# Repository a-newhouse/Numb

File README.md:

# Disclaimer
This is my first attempt, with [Duality](https://github.com/a-newhouse/Duality), to make a fully functional keyboard from A to Z. 
# Schematic
To start with, I knew I wanted to use an RP2040 and per key LEDs. So I searched how to make an RP2040 board amd i found a book made by Raberry PI called the [Hardware design with RP2040: Using RP2040 microcontrollers to build boards and products](./Schematic_&_PCB/Hardware_Design_RP2040.pdf). This book contains alot of information on how to make a RP2040 development board.
# PCB
# 3D modeling
# BOM
# Assembly
# QMK Firmware

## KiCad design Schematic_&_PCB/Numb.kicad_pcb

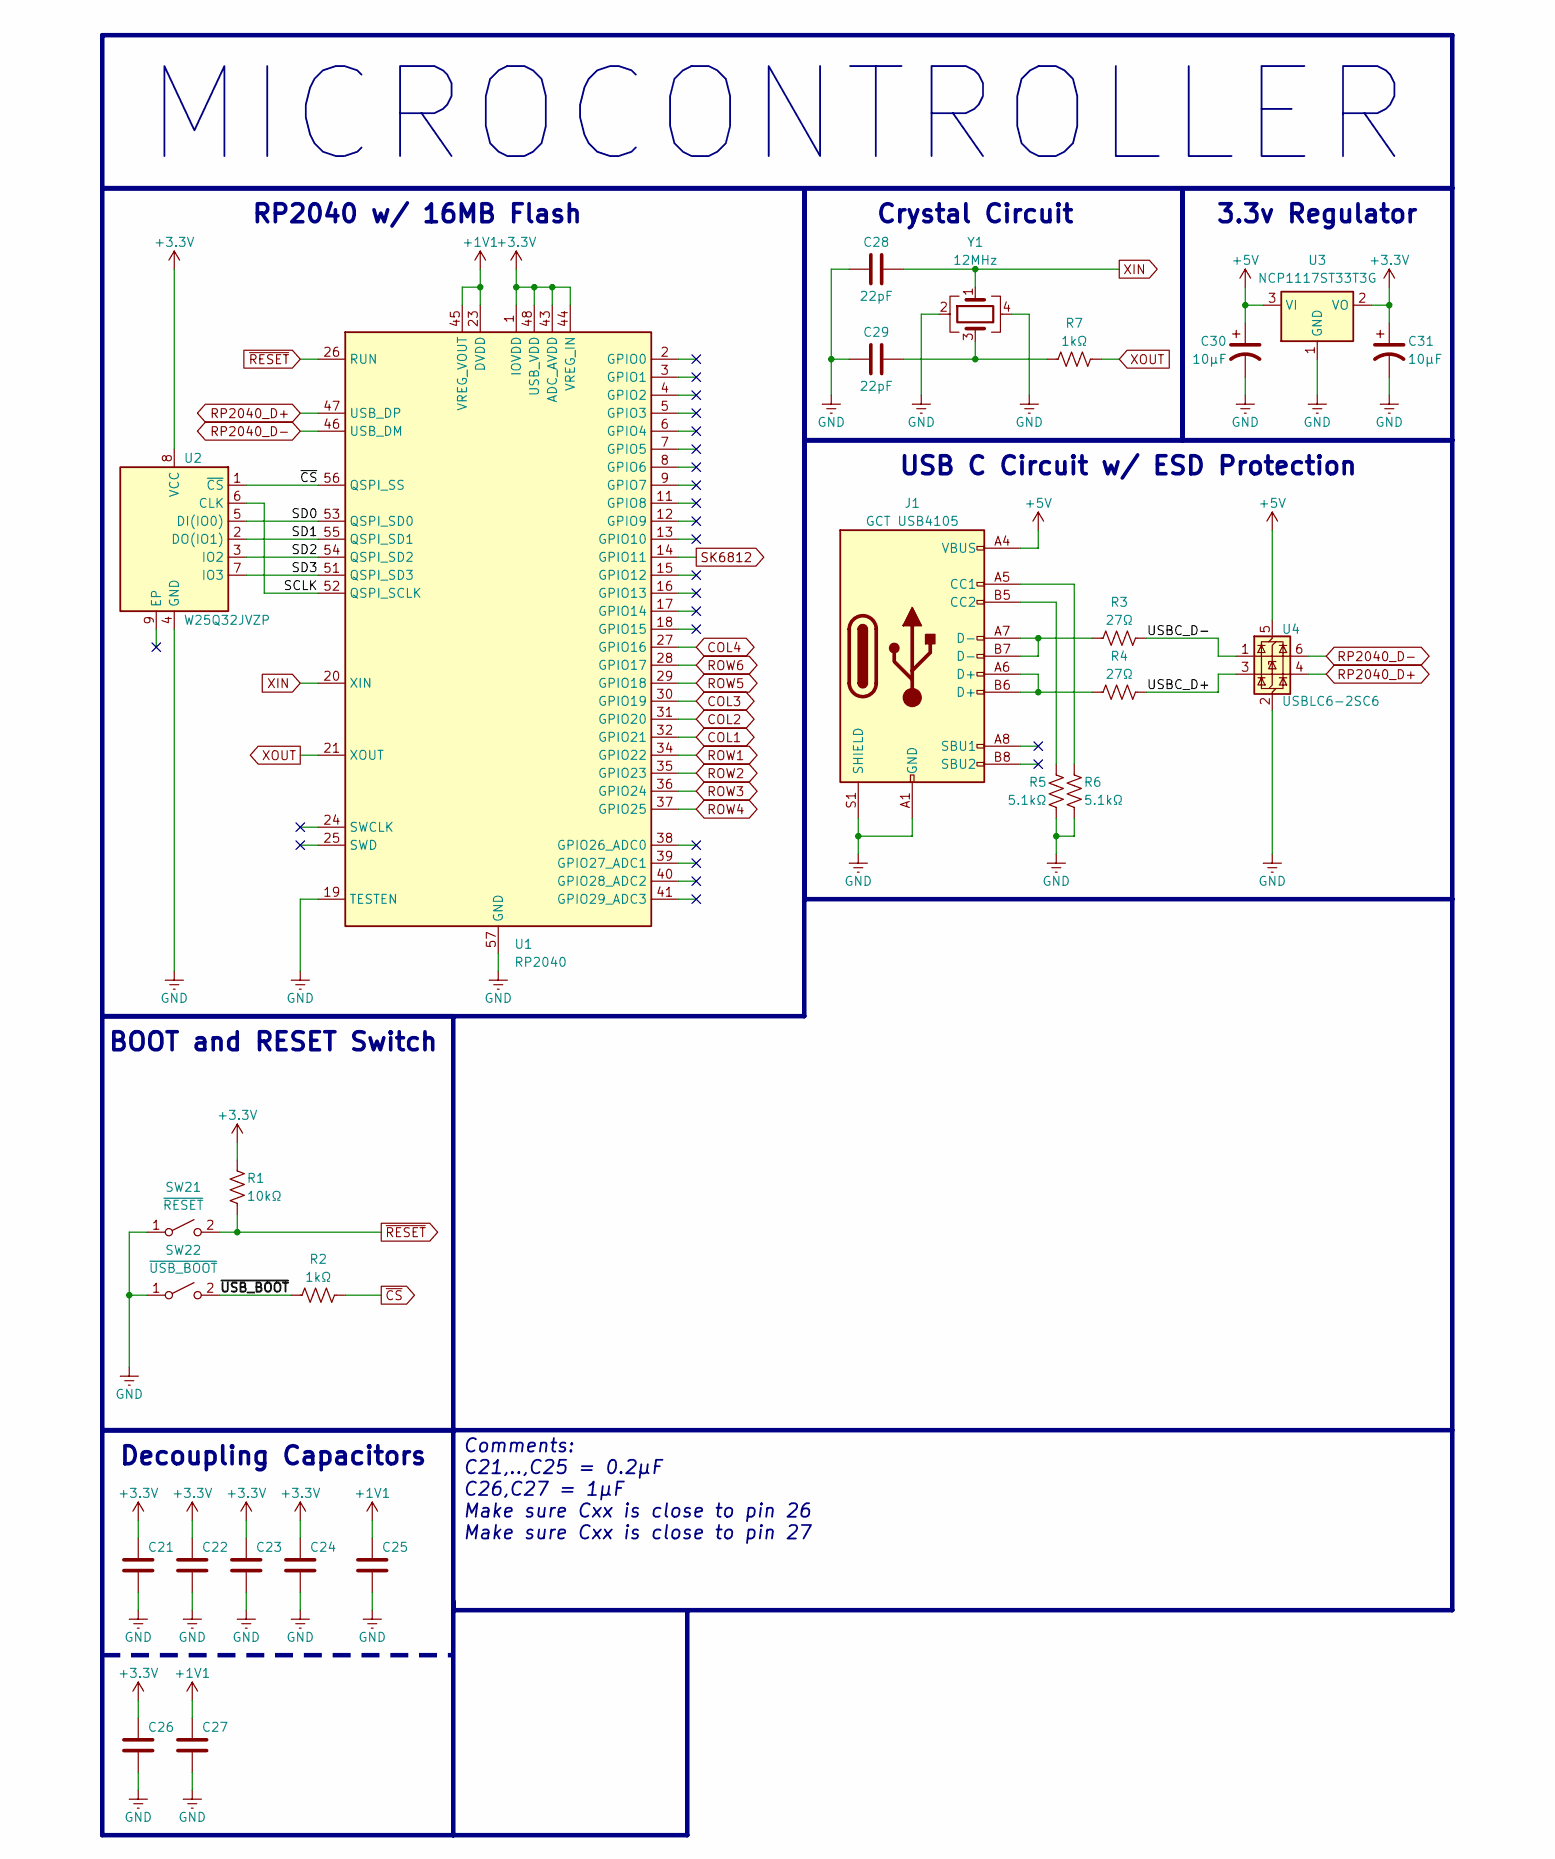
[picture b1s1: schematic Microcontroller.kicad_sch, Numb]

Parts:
C21, C22, C23, C24, C25: 0.2μF; C_0603_1608Metric
C26, C27: 1μF; C_0603_1608Metric
C28, C29: 22pF; C_0402_1005Metric
C30, C31: 10μF; CP_EIA-3216-10_Kemet-I
J1: GCT USB4105; USB_C_Receptacle_GCT_USB4105-xx-A_16P_TopMnt_Horizontal
R1: 10kΩ; R_0402_1005Metric
R2, R7: 1kΩ; R_0402_1005Metric
R3, R4: 27Ω; R_0603_1608Metric
R5, R6: 5.1kΩ; R_0402_1005Metric
SW21: ~{RESET}; SW_SPST_B3U-1000P-B
SW22: ~{USB_BOOT}; SW_SPST_B3U-1000P-B
U1: RP2040; QFN-56-1EP_7x7mm_P0.4mm_EP3.2x3.2mm
U2: W25Q32JVZP; WSON-8-1EP_6x5mm_P1.27mm_EP3.4x4.3mm
U3: NCP1117ST33T3G; SOT-223-3_TabPin2
U4: USBLC6-2SC6; SOT-23-6
Y1: 12MHz; Crystal_SMD_3225-4Pin_3.2x2.5mm

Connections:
+1V1: C25.1, C27.1, U1.23 (DVDD), U1.45 (VREG_VOUT), U1.50 (DVDD)
+3.3V: C21.1, C22.1, C23.1, C24.1, C26.1, C31.1, R1.1, U1.1 (IOVDD), U1.10 (IOVDD), U1.22 (IOVDD), U1.33 (IOVDD), U1.42 (IOVDD), U1.43 (ADC_AVDD), U1.44 (VREG_IN), U1.48 (USB_VDD), U1.49 (IOVDD), U2.8 (VCC), U3.2 (VO)
+5V: C30.1, J1.A4 (VBUS), J1.A9 (VBUS), J1.B4 (VBUS), J1.B9 (VBUS), U3.3 (VI), U4.5 (VBUS); also elsewhere on the board
/Microcontroller/SCLK: U1.52 (QSPI_SCLK), U2.6 (CLK)
/Microcontroller/SD0: U1.53 (QSPI_SD0), U2.5 (DI(IO0))
/Microcontroller/SD1: U1.55 (QSPI_SD1), U2.2 (DO(IO1))
/Microcontroller/SD2: U1.54 (QSPI_SD2), U2.3 (IO2)
/Microcontroller/SD3: U1.51 (QSPI_SD3), U2.7 (IO3)
/Microcontroller/USBC_D+: R4.2, U4.3 (I/O2)
/Microcontroller/USBC_D-: R3.2, U4.1 (I/O1)
/Microcontroller/~USB_BOOT: R2.1, SW22.2 (B)
COL1: U1.32 (GPIO21); also elsewhere on the board
COL2: U1.31 (GPIO20); also elsewhere on the board
COL3: U1.30 (GPIO19); also elsewhere on the board
COL4: U1.27 (GPIO16); also elsewhere on the board
GND: C21.2, C22.2, C23.2, C24.2, C25.2, C26.2, C27.2, C28.1, C29.1, C30.2, C31.2, J1.A1 (GND), J1.A12 (GND), J1.B1 (GND), J1.B12 (GND), J1.S1 (SHIELD), R5.2, R6.2, SW21.1 (A), SW22.1 (A), U1.19 (TESTEN), U1.57 (GND), U2.4 (GND), U3.1 (GND), U4.2 (GND), Y1.2, Y1.4; also elsewhere on the board
unnamed: C29.2, R7.1, Y1.3
unnamed: J1.A5 (CC1), R6.1
unnamed: J1.B5 (CC2), R5.1
unnamed: J1.A6 (D+), J1.B6 (D+), R4.1
unnamed: J1.A7 (D-), J1.B7 (D-), R3.1
ROW1: U1.34 (GPIO22); also elsewhere on the board
ROW2: U1.35 (GPIO23); also elsewhere on the board
ROW3: U1.36 (GPIO24); also elsewhere on the board
ROW4: U1.37 (GPIO25); also elsewhere on the board
ROW5: U1.29 (GPIO18); also elsewhere on the board
ROW6: U1.28 (GPIO17); also elsewhere on the board
RP2040_D+: U1.47 (USB_DP), U4.4 (I/O2)
RP2040_D-: U1.46 (USB_DM), U4.6 (I/O1)
SK6812: U1.14 (GPIO11); also elsewhere on the board
XIN: C28.2, U1.20 (XIN), Y1.1
XOUT: R7.2, U1.21 (XOUT)
~CS: R2.2, U1.56 (QSPI_SS), U2.1 (~CS)
~RESET: R1.2, SW21.2 (B), U1.26 (RUN)

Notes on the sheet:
Crystal Circuit
RP2040 w/ 16MB Flash
3.3v Regulator
Decoupling Capacitors
MICROCONTROLLER
USB C Circuit w/ ESD Protection
Comments: C21,..,C25 = 0.2μF C26,C27 = 1μF Make sure Cxx is close to pin 26 Make sure Cxx is close to pin 27
BOOT and RESET Switch

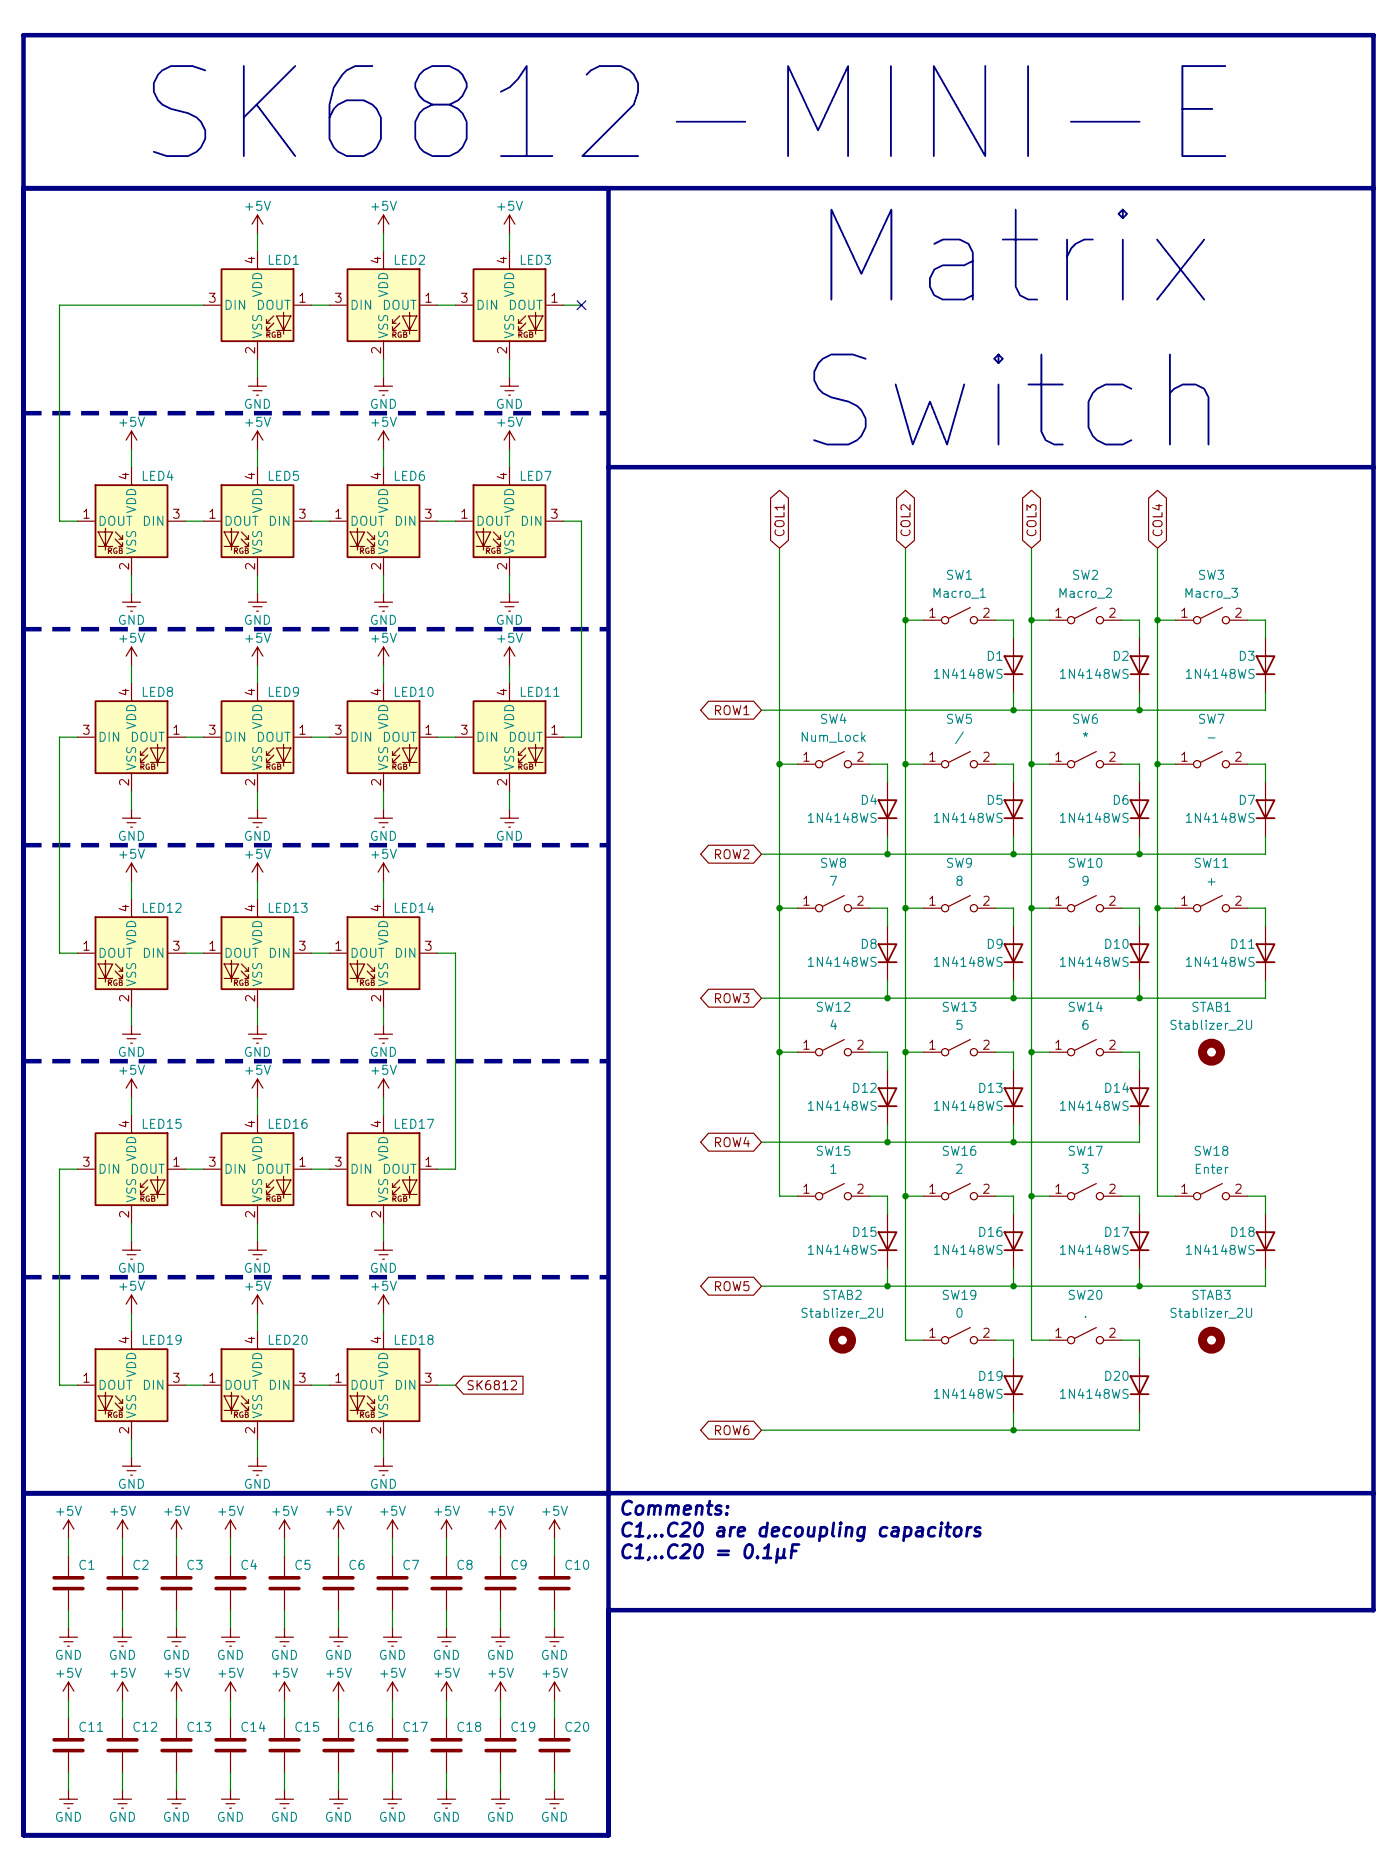
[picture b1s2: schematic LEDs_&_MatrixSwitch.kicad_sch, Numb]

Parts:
C1, C2, C3, C4, C5, C6, C7, C8, C9, C10, C11, C12, C13, C14, C15, C16, C17, C18, C19, C20: 0.1μF; C_0603_1608Metric
D1, D2, D3, D4, D5, D6, D7, D8, D9, D10, D11, D12, D13, D14, D15, D16, D17, D18, D19, D20: 1N4148WS; D_SOD-323
LED1, LED2, LED3, LED8, LED9, LED10, LED11, LED15, LED16, LED17: SK6812MINI-E; SK6812_MINI-E_REV
LED4, LED5, LED6, LED7, LED12, LED13, LED14, LED18, LED19, LED20: SK6812MINI-E; SK6812_MINI-E
STAB1, STAB2, STAB3: Stablizer_2U; Stabilizer_Cherry_MX_2.00u
SW1: Macro_1; SW_Hotswap_Kailh_MX_Plated_1.00u
SW2: Macro_2; SW_Hotswap_Kailh_MX_Plated_1.00u
SW3: Macro_3; SW_Hotswap_Kailh_MX_Plated_1.00u
SW4: Num_Lock; SW_Hotswap_Kailh_MX_Plated_1.00u
SW5: /; SW_Hotswap_Kailh_MX_Plated_1.00u
SW6: *; SW_Hotswap_Kailh_MX_Plated_1.00u
SW7: -; SW_Hotswap_Kailh_MX_Plated_1.00u
SW8: 7; SW_Hotswap_Kailh_MX_Plated_1.00u
SW9: 8; SW_Hotswap_Kailh_MX_Plated_1.00u
SW10: 9; SW_Hotswap_Kailh_MX_Plated_1.00u
SW11: +; SW_Hotswap_Kailh_MX_Plated_2.00u_90deg
SW12: 4; SW_Hotswap_Kailh_MX_Plated_1.00u
SW13: 5; SW_Hotswap_Kailh_MX_Plated_1.00u
SW14: 6; SW_Hotswap_Kailh_MX_Plated_1.00u
SW15: 1; SW_Hotswap_Kailh_MX_Plated_1.00u
SW16: 2; SW_Hotswap_Kailh_MX_Plated_1.00u
SW17: 3; SW_Hotswap_Kailh_MX_Plated_1.00u
SW18: Enter; SW_Hotswap_Kailh_MX_Plated_2.00u_90deg
SW19: 0; SW_Hotswap_Kailh_MX_Plated_2.00u
SW20: .; SW_Hotswap_Kailh_MX_Plated_1.00u

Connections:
+5V: C1.1, C2.1, C3.1, C4.1, C5.1, C6.1, C7.1, C8.1, C9.1, C10.1, C11.1, C12.1, C13.1, C14.1, C15.1, C16.1, C17.1, C18.1, C19.1, C20.1, LED1.4 (VDD), LED2.4 (VDD), LED3.4 (VDD), LED4.4 (VDD), LED5.4 (VDD), LED6.4 (VDD), LED7.4 (VDD), LED8.4 (VDD), LED9.4 (VDD), LED10.4 (VDD), LED11.4 (VDD), LED12.4 (VDD), LED13.4 (VDD), LED14.4 (VDD), LED15.4 (VDD), LED16.4 (VDD), LED17.4 (VDD), LED18.4 (VDD), LED19.4 (VDD), LED20.4 (VDD); also elsewhere on the board
COL1: SW4.1 (A), SW8.1 (A), SW12.1 (A), SW15.1 (A); also elsewhere on the board
COL2: SW1.1 (A), SW5.1 (A), SW9.1 (A), SW13.1 (A), SW16.1 (A), SW19.1 (A); also elsewhere on the board
COL3: SW2.1 (A), SW6.1 (A), SW10.1 (A), SW14.1 (A), SW17.1 (A), SW20.1 (A); also elsewhere on the board
COL4: SW3.1 (A), SW7.1 (A), SW11.1 (A), SW18.1 (A); also elsewhere on the board
GND: C1.2, C2.2, C3.2, C4.2, C5.2, C6.2, C7.2, C8.2, C9.2, C10.2, C11.2, C12.2, C13.2, C14.2, C15.2, C16.2, C17.2, C18.2, C19.2, C20.2, LED1.2 (VSS), LED2.2 (VSS), LED3.2 (VSS), LED4.2 (VSS), LED5.2 (VSS), LED6.2 (VSS), LED7.2 (VSS), LED8.2 (VSS), LED9.2 (VSS), LED10.2 (VSS), LED11.2 (VSS), LED12.2 (VSS), LED13.2 (VSS), LED14.2 (VSS), LED15.2 (VSS), LED16.2 (VSS), LED17.2 (VSS), LED18.2 (VSS), LED19.2 (VSS), LED20.2 (VSS); also elsewhere on the board
unnamed: D1.2 (A), SW1.2 (B)
unnamed: D2.2 (A), SW2.2 (B)
unnamed: D3.2 (A), SW3.2 (B)
unnamed: D4.2 (A), SW4.2 (B)
unnamed: D5.2 (A), SW5.2 (B)
unnamed: D6.2 (A), SW6.2 (B)
unnamed: D7.2 (A), SW7.2 (B)
unnamed: D8.2 (A), SW8.2 (B)
unnamed: D9.2 (A), SW9.2 (B)
unnamed: D10.2 (A), SW10.2 (B)
unnamed: D11.2 (A), SW11.2 (B)
unnamed: D12.2 (A), SW12.2 (B)
unnamed: D13.2 (A), SW13.2 (B)
unnamed: D14.2 (A), SW14.2 (B)
unnamed: D15.2 (A), SW15.2 (B)
unnamed: D16.2 (A), SW16.2 (B)
unnamed: D17.2 (A), SW17.2 (B)
unnamed: D18.2 (A), SW18.2 (B)
unnamed: D19.2 (A), SW19.2 (B)
unnamed: D20.2 (A), SW20.2 (B)
unnamed: LED1.3 (DIN), LED4.1 (DOUT)
unnamed: LED1.1 (DOUT), LED2.3 (DIN)
unnamed: LED2.1 (DOUT), LED3.3 (DIN)
unnamed: LED4.3 (DIN), LED5.1 (DOUT)
unnamed: LED5.3 (DIN), LED6.1 (DOUT)
unnamed: LED6.3 (DIN), LED7.1 (DOUT)
unnamed: LED8.1 (DOUT), LED9.3 (DIN)
unnamed: LED9.1 (DOUT), LED10.3 (DIN)
unnamed: LED10.1 (DOUT), LED11.3 (DIN)
unnamed: LED7.3 (DIN), LED11.1 (DOUT)
unnamed: LED12.3 (DIN), LED13.1 (DOUT)
unnamed: LED8.3 (DIN), LED12.1 (DOUT)
unnamed: LED13.3 (DIN), LED14.1 (DOUT)
unnamed: LED14.3 (DIN), LED17.1 (DOUT)
unnamed: LED15.3 (DIN), LED19.1 (DOUT)
unnamed: LED15.1 (DOUT), LED16.3 (DIN)
unnamed: LED16.1 (DOUT), LED17.3 (DIN)
unnamed: LED18.1 (DOUT), LED20.3 (DIN)
unnamed: LED19.3 (DIN), LED20.1 (DOUT)
ROW1: D1.1 (K), D2.1 (K), D3.1 (K); also elsewhere on the board
ROW2: D4.1 (K), D5.1 (K), D6.1 (K), D7.1 (K); also elsewhere on the board
ROW3: D8.1 (K), D9.1 (K), D10.1 (K), D11.1 (K); also elsewhere on the board
ROW4: D12.1 (K), D13.1 (K), D14.1 (K); also elsewhere on the board
ROW5: D15.1 (K), D16.1 (K), D17.1 (K), D18.1 (K); also elsewhere on the board
ROW6: D19.1 (K), D20.1 (K); also elsewhere on the board
SK6812: LED18.3 (DIN); also elsewhere on the board

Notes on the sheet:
Matrix Switch
Comments: C1,..C20 are decoupling capacitors C1,..C20 = 0.1μF
SK6812-MINI-E

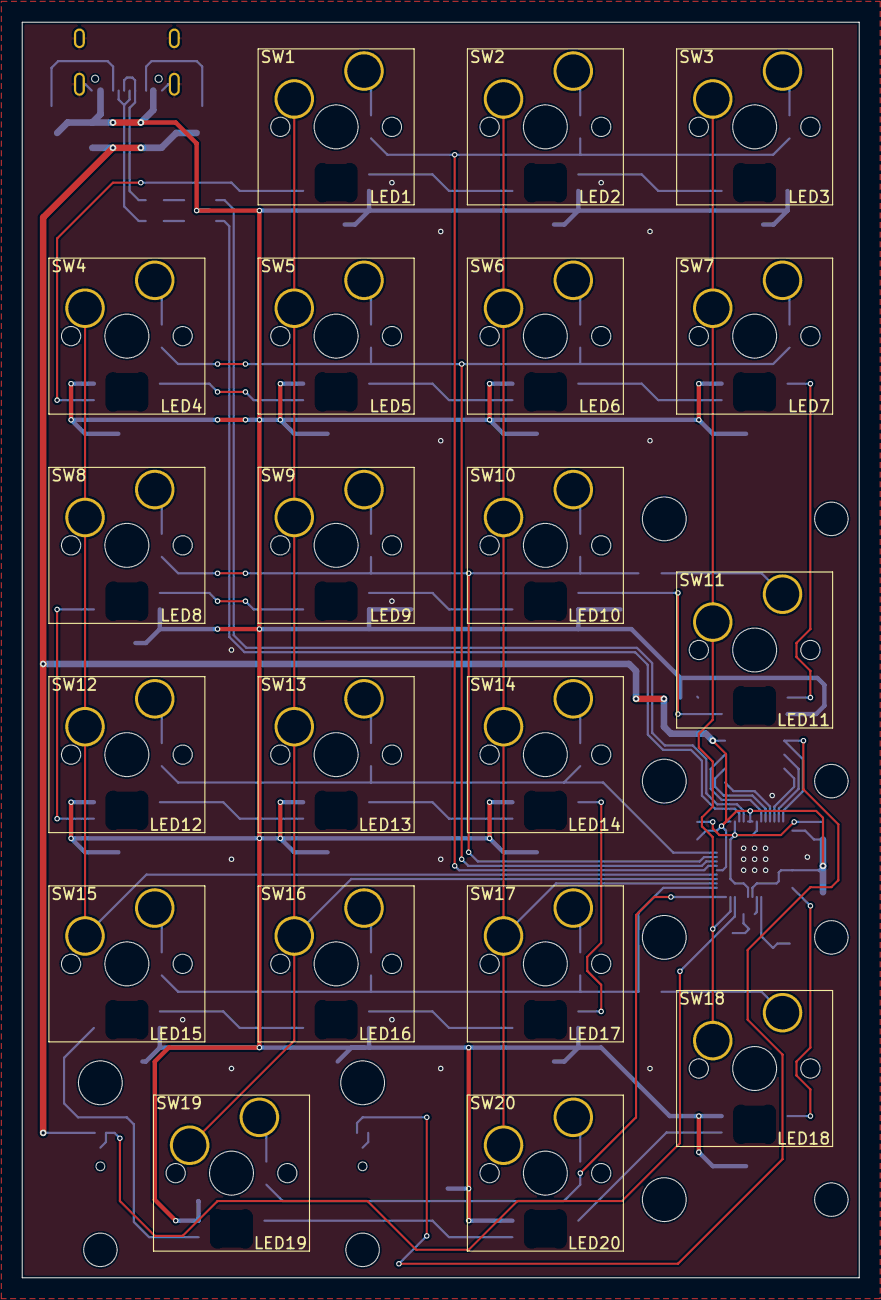
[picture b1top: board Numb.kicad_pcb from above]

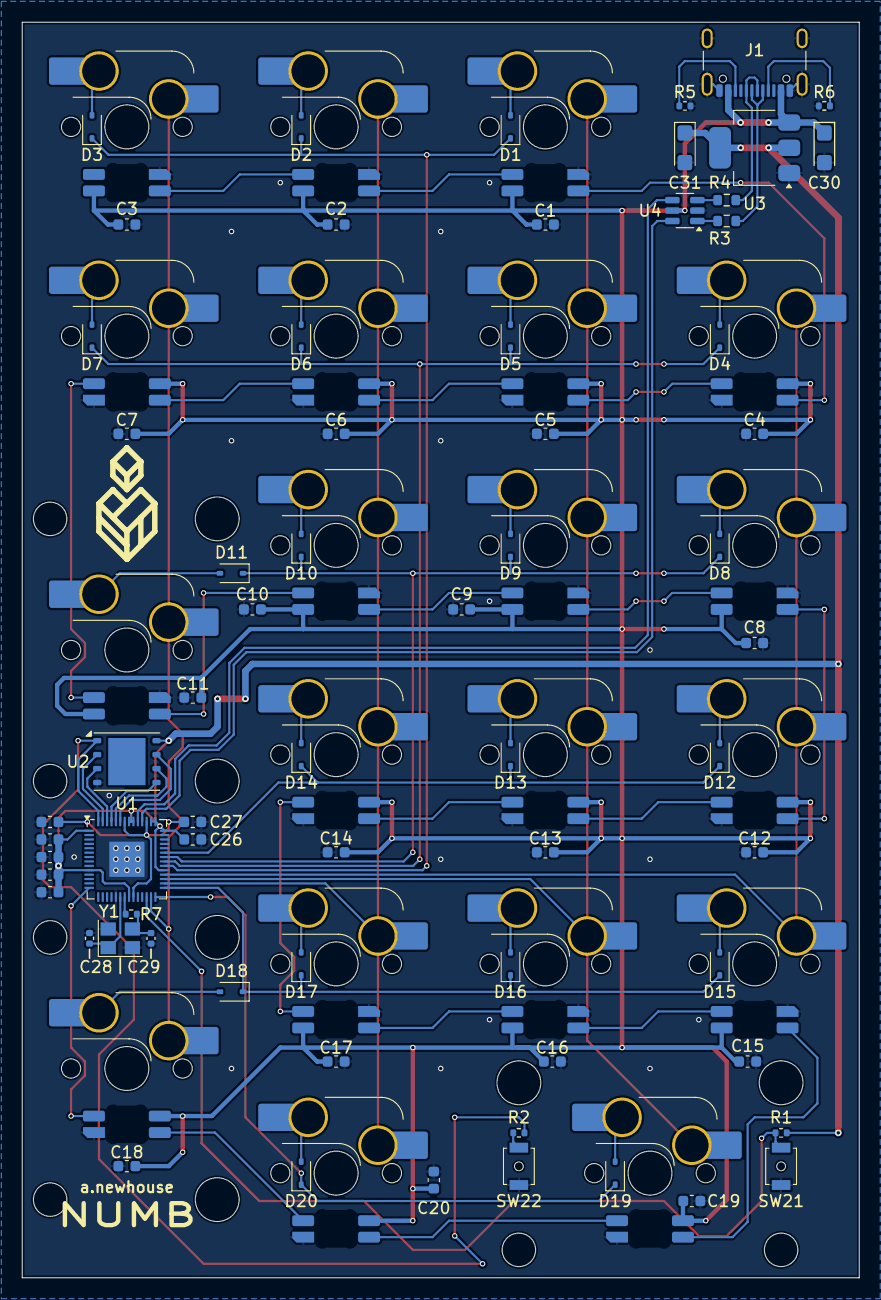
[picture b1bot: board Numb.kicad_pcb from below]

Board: 2 copper layers, 76.2 x 114.3 mm, 109 parts (106 on the bottom side), 73 nets.

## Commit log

2024-12-10 Added Kicad Files
2024-12-16 changed the mcu
